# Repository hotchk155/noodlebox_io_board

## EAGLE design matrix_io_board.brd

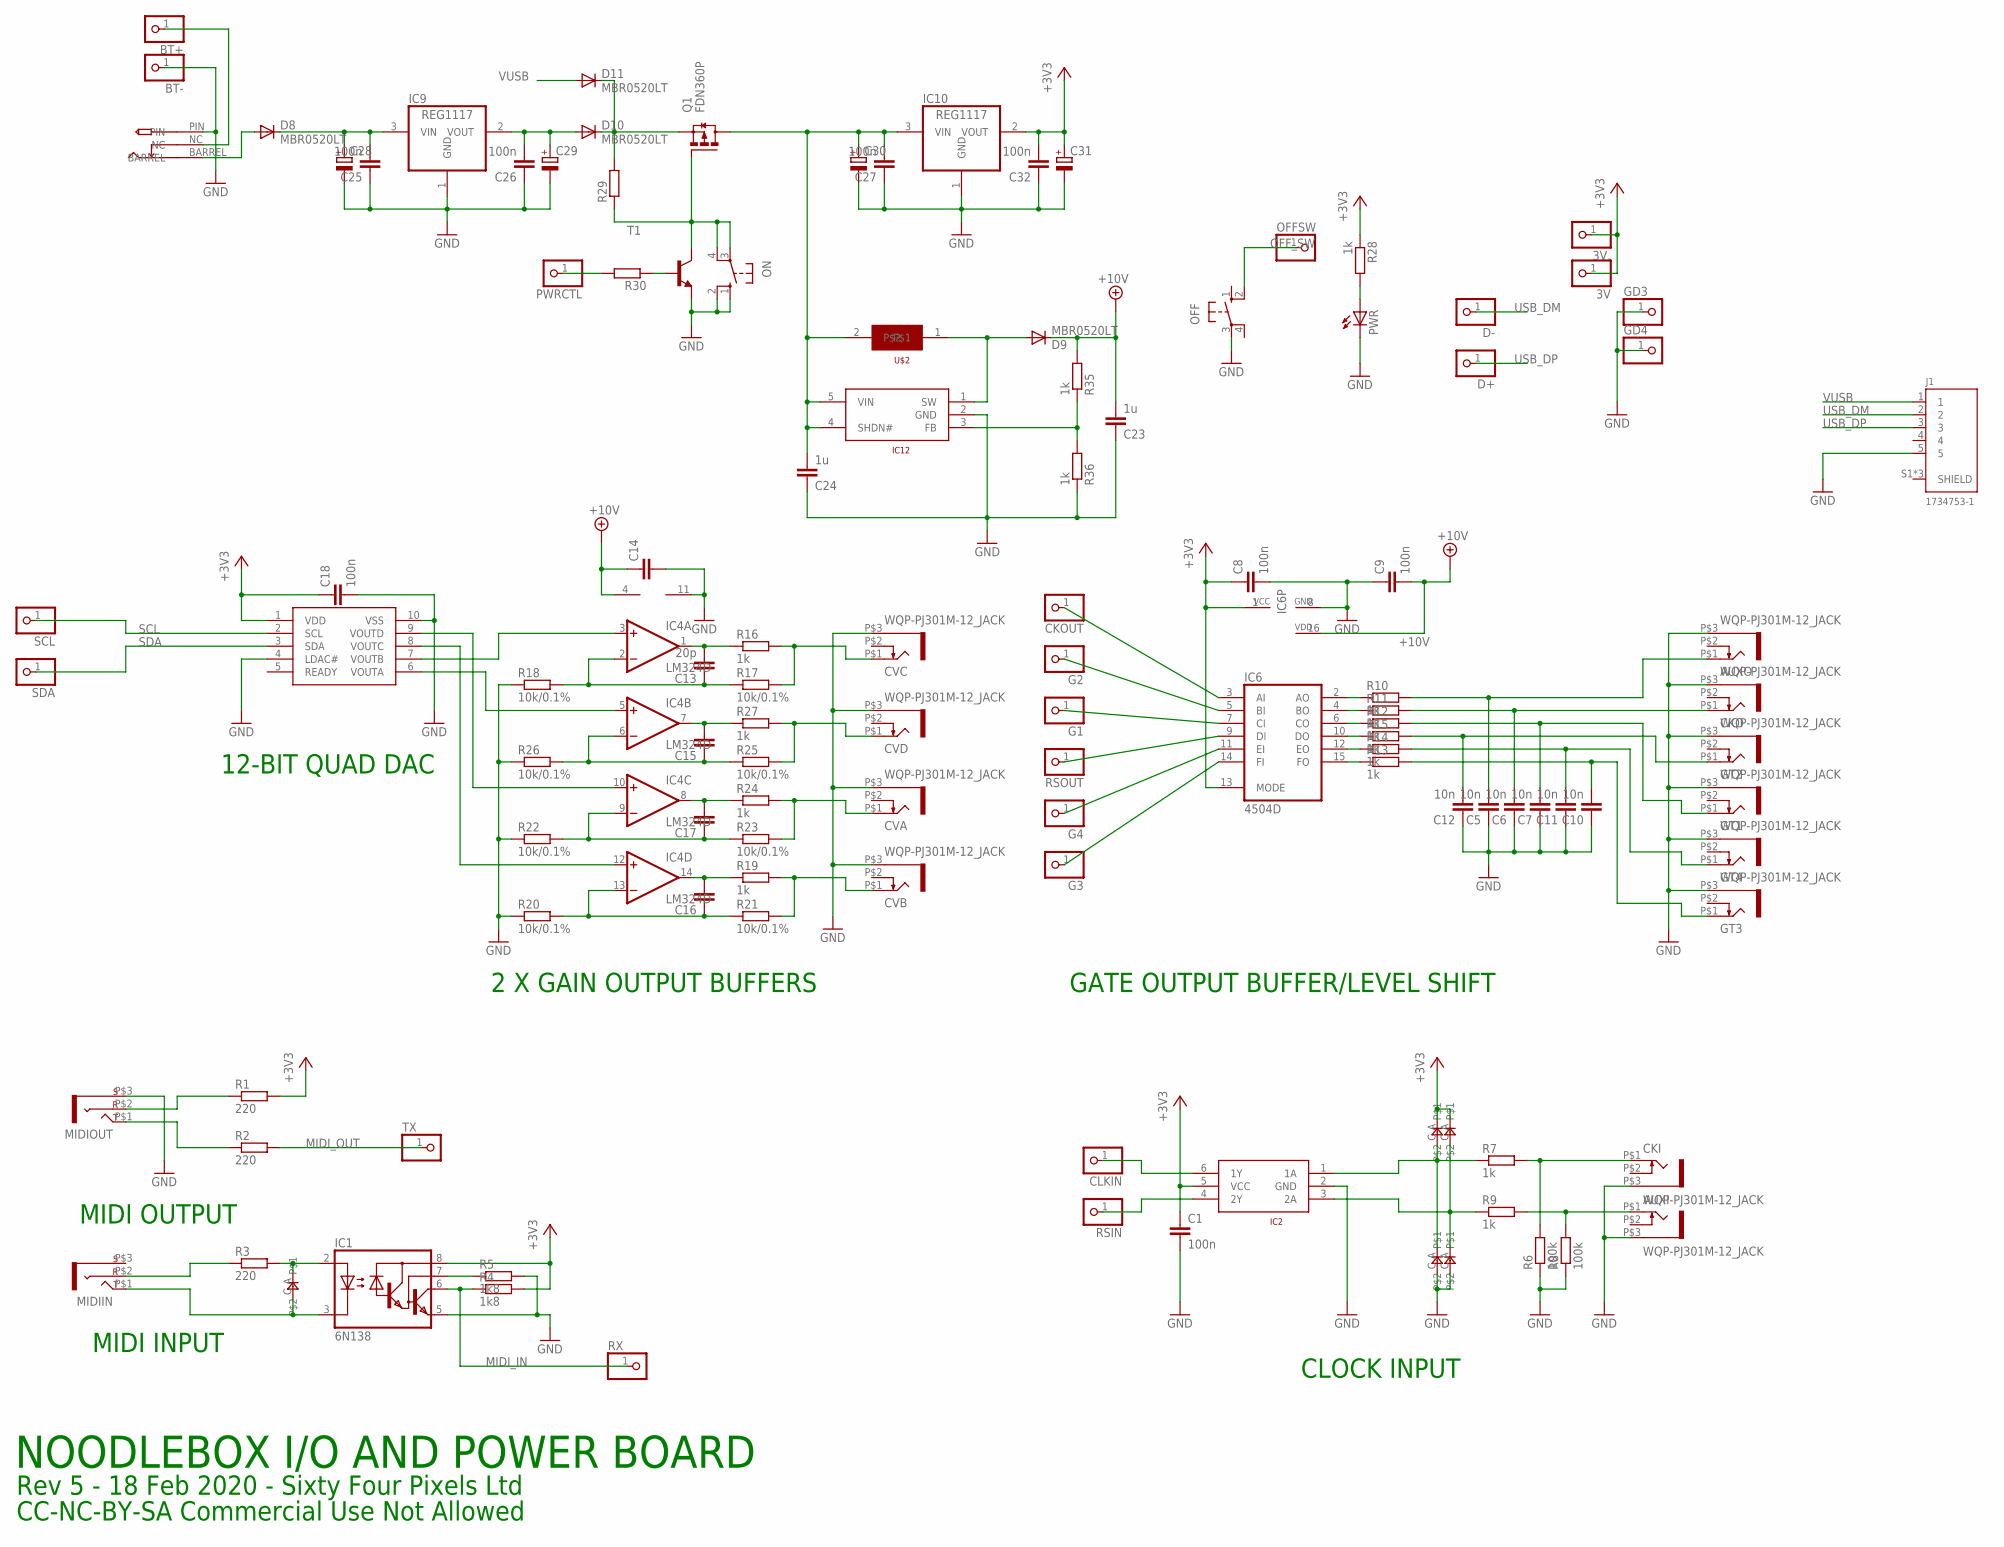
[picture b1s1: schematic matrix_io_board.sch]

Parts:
3V, 3V.: PINHD-1X1; 1X01
AUXI: WQP-PJ301M-12_JACK
AUXO: WQP-PJ301M-12_JACK
BT+: PINHD-1X1; 1X01
BT-: PINHD-1X1; 1X01
C1, C8, C9, C18, C25, C26, C27, C32: 100n; C0805
C5, C6, C7, C10, C11, C12: 10n; C0805
C13: 20p; C0805
C14, C15, C16, C17: C-EUC0805; C0805
C23, C24: 1u; C0805
C28, C29, C30, C31: CPOL-EUD; PANASONIC_D
CKI: WQP-PJ301M-12_JACK
CKO: WQP-PJ301M-12_JACK
CKOUT: PINHD-1X1; 1X01
CLKIN: PINHD-1X1; 1X01
CVA: WQP-PJ301M-12_JACK
CVB: WQP-PJ301M-12_JACK
CVC: WQP-PJ301M-12_JACK
CVD: WQP-PJ301M-12_JACK
D1, D2, D3, D4, D5: 0805DIODE
D8, D9, D10, D11: MBR0520LT; SOD123
D+: PINHD-1X1; 1X01
D-: PINHD-1X1; 1X01
DC: PWR_SOCKET_2_1MM
G1, G2, G3, G4: PINHD-1X1; 1X01
GD3, GD4: PINHD-1X1; 1X01
GT1, GT2, GT3, GT4: WQP-PJ301M-12_JACK
IC1: 6N138; DIL08
IC2: SN74LVC2G14; DBV_R-PDSO-G6
IC4: LM324D; SO14
IC5: MCP4728_QUAD_DAC; MSOP10
IC6: 4504D; SO16
IC9, IC10: REG1117; SOT223
IC12: AP3012; SOT23-5
J1: 1734753-1; CONN_1734753-1
MIDIIN: THONKICONN_STEREO; WQP-PJ301M-ST
MIDIOUT: THONKICONN_STEREO; WQP-PJ301M-ST
OFF: 10-XX; B3F-10XX
OFFSW: PINHD-1X1; 1X01
ON: 10-XX; B3F-10XX
PWR: LED3MM
PWRCTL: PINHD-1X1; 1X01
Q1: FDN360P; SUPER-SOT3
R1, R2, R3: 220; R0805
R4, R5: 1k8; R0805
R6, R8: 100k; R0805
R7, R9, R10, R11, R12, R13, R14, R15, R16, R19, R24, R27, R28, R35, R36: 1k; R0805
R17, R18, R20, R21, R22, R23, R25, R26: 10k/0.1%; R0805
R29, R30: R-EU_R0805; R0805
RSIN: PINHD-1X1; 1X01
RSOUT: PINHD-1X1; 1X01
RX: PINHD-1X1; 1X01
SCL: PINHD-1X1; 1X01
SDA: PINHD-1X1; 1X01
T1: MMBT3904LT1-NPN-SOT23-BEC; SOT23-BEC
TX: PINHD-1X1; 1X01
U$2: CDRH3D14

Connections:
+3V3: 3V.1, 3V..1, C1.1, C8.1, C18.1, C31.+, C32.2, D3.A, D4.A, IC1.8 (VCC), IC2.5 (VCC), IC5.1 (VDD), IC6.1 (VCC), IC6.13 (MODE), IC10.2 (VOUT), R1.2, R4.2, R28.1
+10V: C9.2, C14.1, C23.2, D9.C, IC4.4 (V+), IC6.16 (VDD), R35.2
AUXGATE: IC6.9 (DI), RSOUT.1
CLKOUT: CKOUT.1, IC6.3 (AI)
GATE1: G3.1, IC6.14 (FI)
GATE2: G2.1, IC6.5 (BI)
GATE3: G1.1, IC6.7 (CI)
GATE4: G4.1, IC6.11 (EI)
GND: AUXI.P$3 (1), AUXO.P$3 (1), BT-.1, C1.2, C5.1, C6.1, C7.1, C8.2, C9.1, C10.1, C11.1, C12.1, C14.2, C18.2, C23.1, C24.1, C25.1, C26.1, C27.1, C28.-, C29.-, C30.-, C31.-, C32.1, CKI.P$3 (1), CKO.P$3 (1), CVA.P$3 (1), CVB.P$3 (1), CVC.P$3 (1), CVD.P$3 (1), D2.C, D5.C, DC.PIN, GD3.1, GD4.1, GT1.P$3 (1), GT2.P$3 (1), GT3.P$3 (1), GT4.P$3 (1), IC1.5 (GND), IC2.2 (GND), IC4.11 (V-), IC5.4 (LDAC#), IC5.10 (VSS), IC6.8 (GND), IC9.1 (GND), IC10.1 (GND), IC12.2 (GND), J1.5, MIDIOUT.P$3 (S), OFF.3, ON.1 (S), ON.2 (S1), PWR.K (C), R5.2, R6.1, R8.1, R18.1, R20.1, R22.1, R26.1, R36.1, T1.E
MIDI_IN: IC1.6 (VO), R4.1, RX.1
MIDI_OUT: R2.2, TX.1
unnamed: MIDIOUT.P$2 (R), R1.1
unnamed: D1.A, IC1.2 (A), R3.2
unnamed: IC4.3 (+IN), IC5.7 (VOUTB)
unnamed: D1.C, IC1.3 (C), MIDIIN.P$1 (T)
unnamed: IC1.7 (VB), R5.1
unnamed: MIDIOUT.P$1 (T), R2.1
unnamed: MIDIIN.P$2 (R), R3.1
unnamed: CVC.P$1 (2), R16.2, R17.2
unnamed: CVD.P$1 (2), R25.2, R27.2
unnamed: CVB.P$1 (2), R19.2, R21.2
unnamed: CVA.P$1 (2), R23.2, R24.2
unnamed: C13.2, IC4.1 (OUT), R16.1
unnamed: C15.2, IC4.7 (OUT), R27.1
unnamed: C17.2, IC4.8 (OUT), R24.1
unnamed: C16.2, IC4.14 (OUT), R19.1
unnamed: BT+.1, DC.NC
unnamed: C16.1, IC4.13 (-IN), R20.2, R21.1
unnamed: C17.1, IC4.9 (-IN), R22.2, R23.1
unnamed: IC6.10 (DO), R15.1
unnamed: C15.1, IC4.6 (-IN), R25.1, R26.2
unnamed: C26.2, C29.+, D10.A, IC9.2 (VOUT)
unnamed: C13.1, IC4.2 (-IN), R17.1, R18.2
unnamed: CLKIN.1, IC2.6 (1Y)
unnamed: AUXI.P$1 (2), R8.2, R9.2
unnamed: IC2.4 (2Y), RSIN.1
unnamed: D4.C, D5.A, IC2.3 (2A), R9.1
unnamed: C12.2, GT2.P$1 (2), R15.2
unnamed: D9.A, IC12.1 (SW), U$2.1
unnamed: IC4.5 (+IN), IC5.6 (VOUTA)
unnamed: IC4.10 (+IN), IC5.9 (VOUTD)
unnamed: IC4.12 (+IN), IC5.8 (VOUTC)
unnamed: D10.C, D11.C, Q1.2 (S), R29.2
unnamed: C24.2, C27.2, C30.+, IC10.3 (VIN), IC12.4 (SHDN#), IC12.5 (VIN), Q1.3 (D), U$2.2
unnamed: ON.3, ON.4 (P1), Q1.1 (G), R29.1, T1.C
unnamed: R30.1, T1.B
unnamed: D8.A, DC.BARREL
unnamed: IC6.2 (AO), R10.1
unnamed: C25.2, C28.+, D8.C, IC9.3 (VIN)
unnamed: IC6.4 (BO), R11.1
unnamed: IC6.6 (CO), R12.1
unnamed: PWRCTL.1, R30.2
unnamed: IC6.12 (EO), R14.1
unnamed: AUXO.P$1 (2), C5.2, R10.2
unnamed: C6.2, CKO.P$1 (2), R11.2
unnamed: C7.2, GT1.P$1 (2), R12.2
unnamed: C11.2, GT4.P$1 (2), R14.2
unnamed: C10.2, GT3.P$1 (2), R13.2
unnamed: IC6.15 (FO), R13.1
unnamed: IC12.3 (FB), R35.1, R36.2
unnamed: D2.A, D3.C, IC2.1 (1A), R7.1
unnamed: CKI.P$1 (2), R6.2, R7.2
unnamed: PWR.A, R28.2
OFF_SW: OFF.2 (S1), OFFSW.1
SCL: IC5.2 (SCL), SCL.1
SDA: IC5.3 (SDA), SDA.1
USB_DM: D-.1, J1.2
USB_DP: D+.1, J1.3
VUSB: D11.A, J1.1

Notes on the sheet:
2 X GAIN OUTPUT BUFFERS
12-BIT QUAD DAC
GATE OUTPUT BUFFER/LEVEL SHIFT
MIDI INPUT
MIDI OUTPUT
CLOCK INPUT
NOODLEBOX I/O AND POWER BOARD
Rev 5 - 18 Feb 2020 - Sixty Four Pixels Ltd
CC-NC-BY-SA Commercial Use Not Allowed

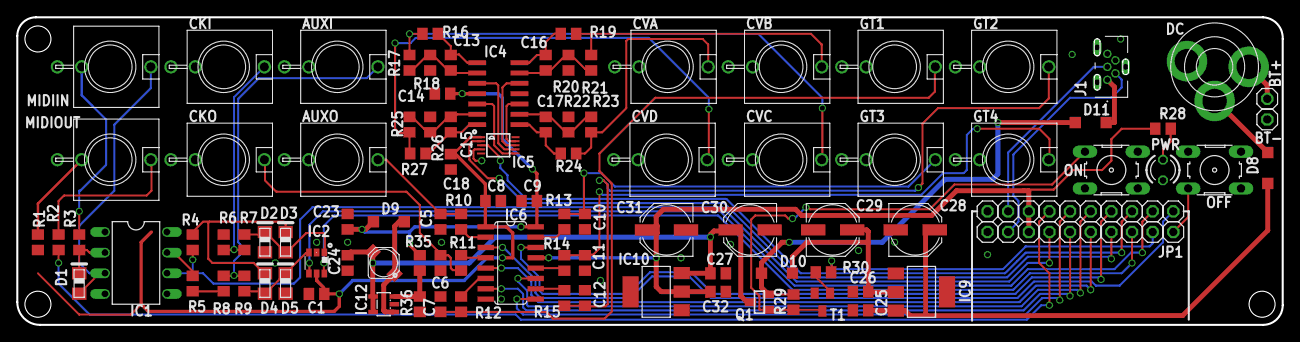
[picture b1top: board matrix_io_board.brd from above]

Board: 2 copper layers, 155.7 x 37.8 mm, 118 parts (0 on the bottom side), 69 nets.

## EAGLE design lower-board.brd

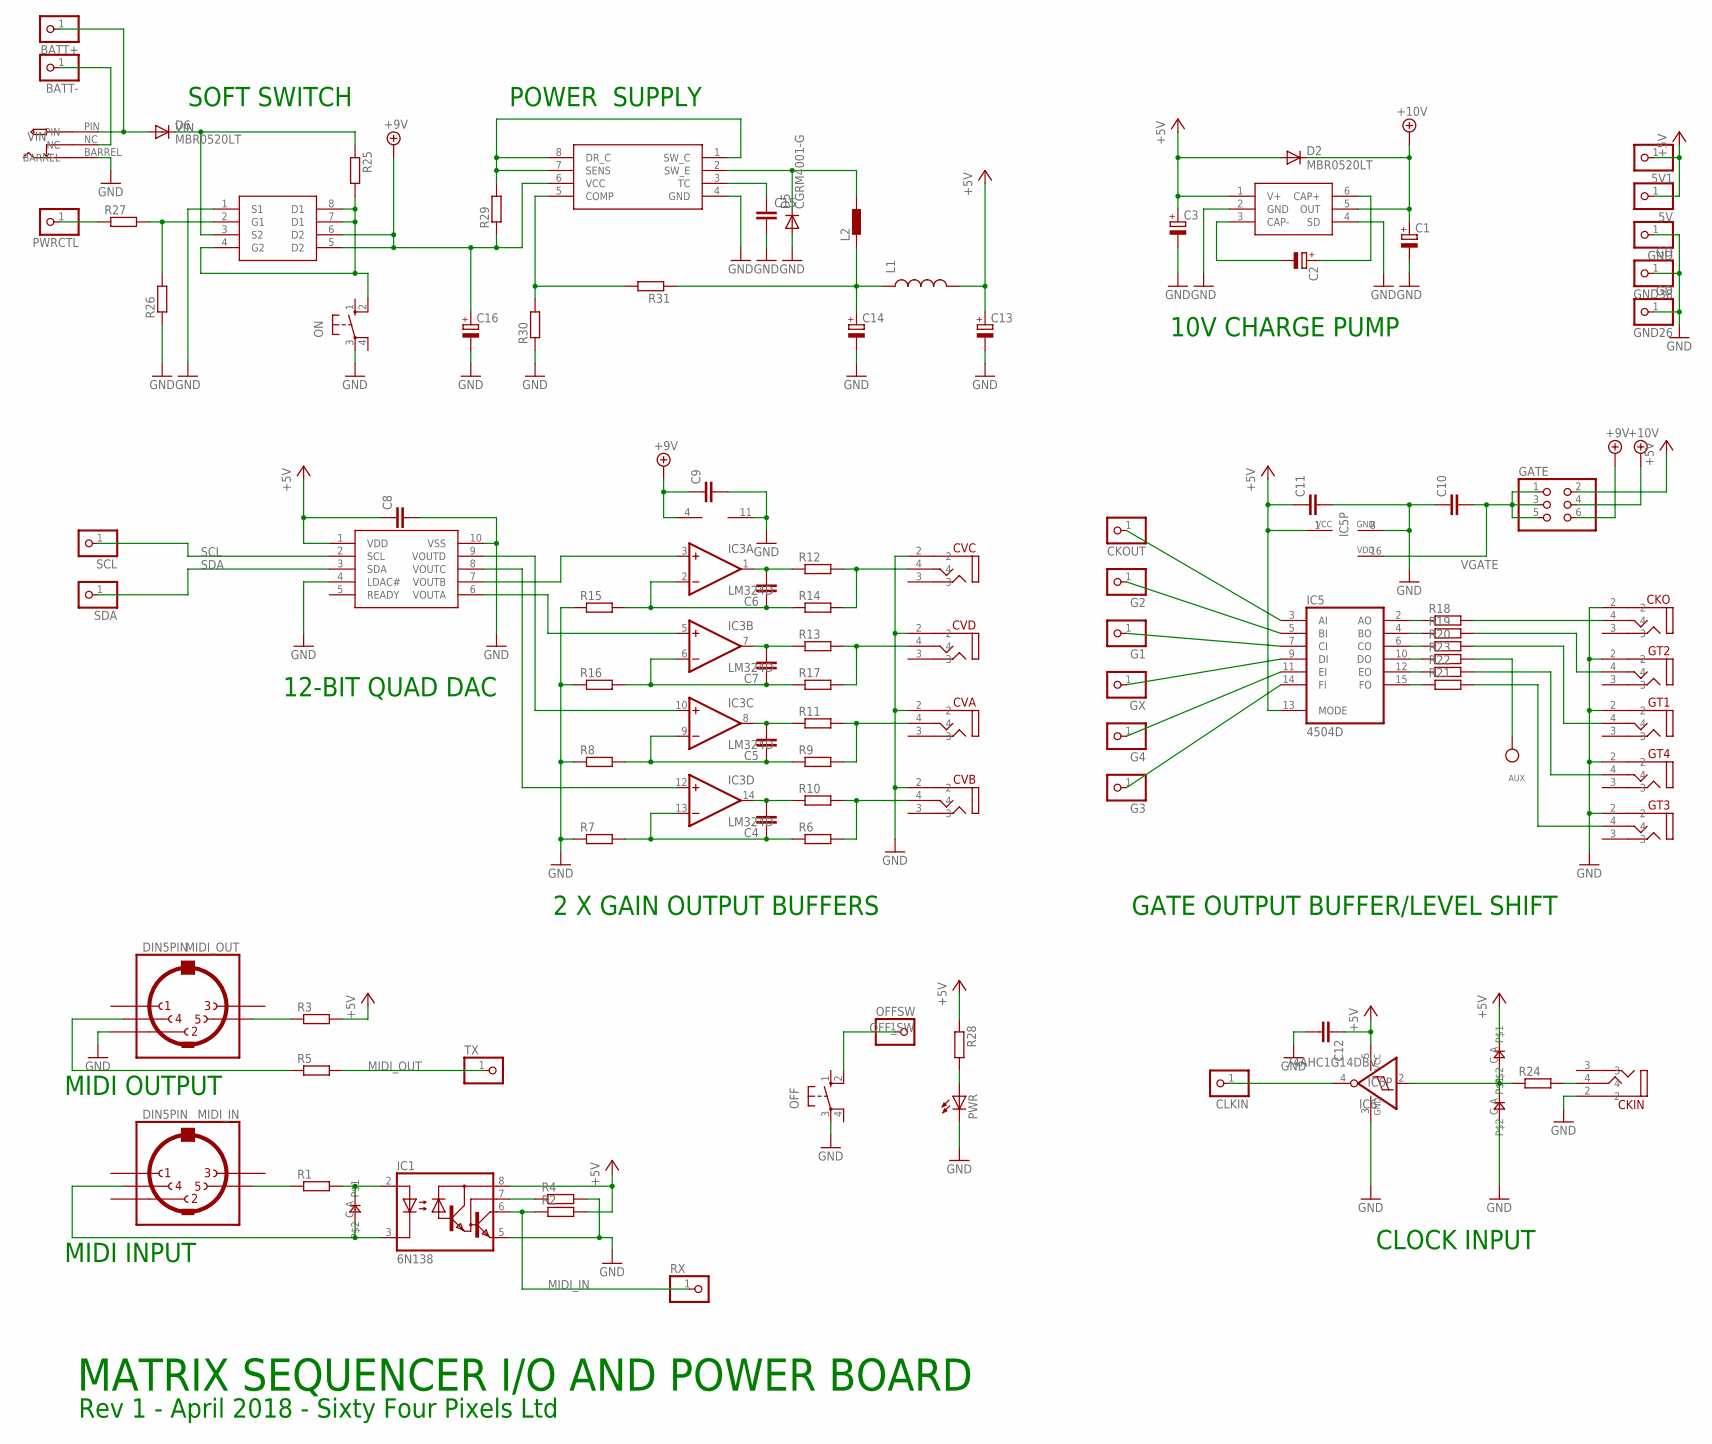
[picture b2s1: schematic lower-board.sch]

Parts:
5V, 5V1: PINHD-1X1; 1X01
AUX: TESTPOINTROUND2MM; TESTPOINT_ROUND_2MM
BATT+: PINHD-1X1; 1X01
BATT-: PINHD-1X1; 1X01
C1, C2, C3: CPOL-EUSMCA; SMC_A
C4, C5, C6, C7, C8, C9, C10, C11, C12, C15: C-EUC0805; C0805
C13, C14, C16: CPOL-EUE2.5-7; E2,5-7
CKIN: VERTICAL_3_5MM_SOCKET
CKO: VERTICAL_3_5MM_SOCKET
CKOUT: PINHD-1X1; 1X01
CLKIN: PINHD-1X1; 1X01
CVA: VERTICAL_3_5MM_SOCKET
CVB: VERTICAL_3_5MM_SOCKET
CVC: VERTICAL_3_5MM_SOCKET
CVD: VERTICAL_3_5MM_SOCKET
D1, D3, D4: 0805DIODE
D2, D6: MBR0520LT; SOD123
D5: CGRM4001-G; SOD-123_MINI-SMA
G1, G2, G3, G4: PINHD-1X1; 1X01
GATE: PINHD-2X3; 2X03
GND: PINHD-1X1; 1X01
GND26, GND38: GD; 1X01
GT1, GT2, GT3, GT4: VERTICAL_3_5MM_SOCKET
GX: PINHD-1X1; 1X01
IC1: 6N138; DIL08
IC2: LM27675M5_CHARGEPUMP; SOT23-6
IC3: LM324D; SO14
IC4: MCP4728_QUAD_DAC; MSOP10
IC5: 4504D; SO16
IC6: 74AHC1G14DBV; SOT23-5
IC7: FDS8958B; SOIC8
IC8: SP34063A_BOOST_REG; SOIC8
L1: INDUCTOR1210; 1210
L2: DR1030
MIDI_IN: DIN5PIN; EDGEDIN
MIDI_OUT: DIN5PIN; EDGEDIN
OFF: 10-XX; B3F-10XX
OFFSW: PINHD-1X1; 1X01
ON: 10-XX; B3F-10XX
PWR: LED3MM
PWRCTL: PINHD-1X1; 1X01
R1, R2, R3, R4, R5, R6, R7, R8, R9, R10, R11, R12, R13, R14, R15, R16, R17, R18, R19, R20, R21, R22, R23, R24, R25, R26, R27, R28, R29, R30, R31: R-EU_R0805; R0805
RX: PINHD-1X1; 1X01
SCL: PINHD-1X1; 1X01
SDA: PINHD-1X1; 1X01
TX: PINHD-1X1; 1X01
U$1: PWR_SOCKET_2_1MM

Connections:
+5V: 5V.1, 5V1.1, C3.+, C8.1, C11.1, C12.1, C13.+, D2.A, D3.A, GATE.2, IC1.8 (VCC), IC2.1 (V+), IC4.1 (VDD), IC5.1 (VCC), IC5.13 (MODE), IC6.5 (VCC), L1.2, R2.2, R3.2, R28.1
+9V: C9.1, C16.+, GATE.6, IC3.4 (V+), IC7.5 (D2), IC7.6 (D2), IC8.6 (VCC), R29.1
+10V: C1.+, D2.C, GATE.4, IC2.5 (OUT)
AUXGATE: GX.1, IC5.9 (DI)
CLKIN: CLKIN.1, IC6.4 (O)
CLKOUT: CKOUT.1, IC5.3 (AI)
GATE1: G3.1, IC5.14 (FI)
GATE2: G2.1, IC5.5 (BI)
GATE3: G1.1, IC5.7 (CI)
GATE4: G4.1, IC5.11 (EI)
GND: C1.-, C3.-, C8.2, C9.2, C10.1, C11.2, C12.2, C13.-, C14.-, C15.2, C16.-, CKIN.2, CKO.2, CVA.2, CVB.2, CVC.2, CVD.2, D4.C, D5.A, GND.1, GND26.1, GND38.1, GT1.2, GT2.2, GT3.2, GT4.2, IC1.5 (GND), IC2.2 (GND), IC2.4 (SD), IC3.11 (V-), IC4.4 (LDAC#), IC4.10 (VSS), IC5.8 (GND), IC6.3 (GND), IC7.1 (S1), IC8.4 (GND), MIDI_OUT.2, OFF.3, ON.3, PWR.K (C), R4.2, R7.1, R8.1, R15.1, R16.1, R26.1, R30.1, U$1.BARREL
MIDI_IN: IC1.6 (VO), R2.1, RX.1
MIDI_OUT: R5.2, TX.1
unnamed: MIDI_OUT.5, R3.1
unnamed: D1.A, IC1.2 (A), R1.2
unnamed: IC3.3 (+IN), IC4.7 (VOUTB)
unnamed: D1.C, IC1.3 (C), MIDI_IN.4
unnamed: IC1.7 (VB), R4.1
unnamed: MIDI_OUT.4, R5.1
unnamed: MIDI_IN.5, R1.1
unnamed: CVC.4, R12.2, R14.2
unnamed: CVD.4, R13.2, R17.2
unnamed: CVB.4, R6.2, R10.2
unnamed: CVA.4, R9.2, R11.2
unnamed: C6.2, IC3.1 (OUT), R12.1
unnamed: C7.2, IC3.7 (OUT), R13.1
unnamed: C5.2, IC3.8 (OUT), R11.1
unnamed: C4.2, IC3.14 (OUT), R10.1
unnamed: C4.1, IC3.13 (-IN), R6.1, R7.2
unnamed: C5.1, IC3.9 (-IN), R8.2, R9.1
unnamed: C7.1, IC3.6 (-IN), R16.2, R17.1
unnamed: C6.1, IC3.2 (-IN), R14.1, R15.2
unnamed: IC3.5 (+IN), IC4.6 (VOUTA)
unnamed: IC3.10 (+IN), IC4.9 (VOUTD)
unnamed: IC3.12 (+IN), IC4.8 (VOUTC)
unnamed: IC8.1 (SW_C), IC8.7 (SENS), IC8.8 (DR_C), R29.2
unnamed: IC8.5 (COMP), R30.2, R31.2
unnamed: C15.1, IC8.3 (TC)
unnamed: D5.C, IC8.2 (SW_E), L2.2
unnamed: BATT+.1, D6.A, U$1.PIN
unnamed: IC5.2 (AO), R18.1
unnamed: C2.+, IC2.6 (CAP+)
unnamed: C2.-, IC2.3 (CAP-)
unnamed: IC5.4 (BO), R19.1
unnamed: IC5.6 (CO), R20.1
unnamed: IC5.10 (DO), R23.1
unnamed: IC5.12 (EO), R22.1
unnamed: CKO.4, R18.2
unnamed: GT2.4, R19.2
unnamed: GT1.4, R20.2
unnamed: GT4.4, R22.2
unnamed: GT3.4, R21.2
unnamed: IC5.15 (FO), R21.1
unnamed: AUX.P$1, R23.2
unnamed: C14.+, L1.1, L2.1, R31.1
unnamed: D3.C, D4.A, IC6.2 (I), R24.1
unnamed: CKIN.4, R24.2
unnamed: PWR.A, R28.2
unnamed: IC7.4 (G2), IC7.7 (D1), IC7.8 (D1), ON.2 (S1), R25.2
unnamed: IC7.2 (G1), R26.2, R27.2
unnamed: BATT-.1, U$1.NC
OFF_SW: OFF.2 (S1), OFFSW.1
PWR_CTRL: PWRCTL.1, R27.1
SCL: IC4.2 (SCL), SCL.1
SDA: IC4.3 (SDA), SDA.1
VGATE: C10.2, GATE.1, GATE.3, GATE.5, IC5.16 (VDD)
VIN: D6.C, IC7.3 (S2), R25.1

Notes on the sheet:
POWER SUPPLY
SOFT SWITCH
2 X GAIN OUTPUT BUFFERS
12-BIT QUAD DAC
GATE OUTPUT BUFFER/LEVEL SHIFT
10V CHARGE PUMP
MIDI INPUT
MIDI OUTPUT
CLOCK INPUT
MATRIX SEQUENCER I/O AND POWER BOARD
Rev 1 - April 2018 - Sixty Four Pixels Ltd

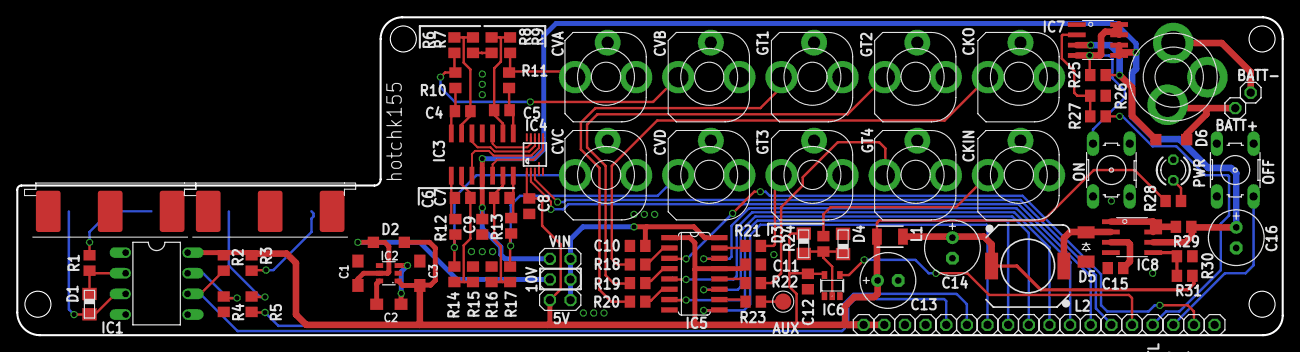
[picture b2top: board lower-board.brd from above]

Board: 2 copper layers, 155.7 x 39.1 mm, 101 parts (0 on the bottom side), 67 nets.

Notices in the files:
matrix_io_board.brd:
CC-BY-NC-SA
